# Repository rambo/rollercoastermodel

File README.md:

rollercoastermodel
==================

Schematics and Arduino code related to a model rollercoaster

This was done to help Stadi Mallarit to get some new tools by building the model
to company X (I'll check later if they want their name released).

I ran out of time so some features (like adjusting each LED channel via the menu)
are not implemented at all, and the state machine for the menu in general is a bit
of a mess. It does work though.

The reason for some "weirdness" in the schematics of the IO boards is that those
were built on veroboard (in retrospect it would have been faster to make proper boards
even with all the drilling involved).

If I end up doing this menu thing better in some other project I'll come back here
and add a link, meanwhile: Be brave even if it looks like a horrible mess, there is some
decent stuff hidden in there.

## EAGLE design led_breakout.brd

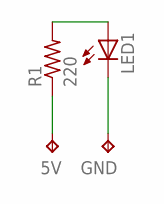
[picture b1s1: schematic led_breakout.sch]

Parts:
5V: TPTP13R; TP13R
GND: TPTP13SQ; TP13SQ
LED1: LEDSML0603; SML0603
R1: 220; R0603

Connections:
5V: 5V.TP, R1.1
GND: GND.TP, LED1.C
LEDSUPPLY: LED1.A, R1.2

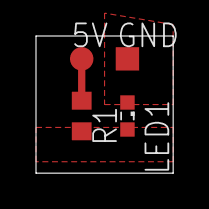
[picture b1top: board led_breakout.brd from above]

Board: 2 copper layers, 7.6 x 7.6 mm, 4 parts (0 on the bottom side), 3 nets.

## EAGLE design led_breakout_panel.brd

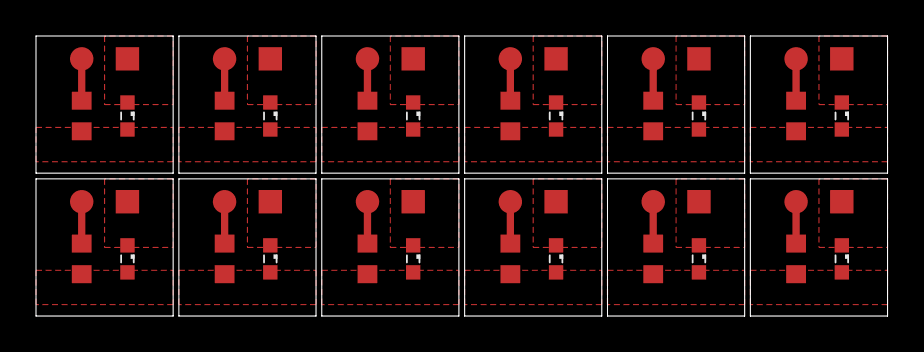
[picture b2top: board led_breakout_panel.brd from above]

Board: 2 copper layers, 47.3 x 15.6 mm, 48 parts (0 on the bottom side), 36 nets.

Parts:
5V, 5V1, 5V2, 5V3, 5V4, 5V5, 5V6, 5V7, 5V8, 5V9, 5V10, 5V11: TPTP13R; TP13R
GND, GND1, GND2, GND3, GND4, GND5, GND6, GND7, GND8, GND9, GND10, GND11: TPTP13SQ; TP13SQ
LED1, LED2, LED3, LED4, LED5, LED6, LED7, LED8, LED9, LED10, LED11, LED12: SML0603
R1, R2, R3, R4, R5, R6, R7, R8, R9, R10, R11, R12: 220; R0603

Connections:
5V: 5V.TP, R1.1
5V1: 5V1.TP, R2.1
5V2: 5V2.TP, R3.1
5V3: 5V3.TP, R4.1
5V4: 5V4.TP, R5.1
5V5: 5V5.TP, R6.1
5V6: 5V6.TP, R7.1
5V7: 5V7.TP, R8.1
5V8: 5V8.TP, R9.1
5V9: 5V9.TP, R10.1
5V10: 5V10.TP, R11.1
5V11: 5V11.TP, R12.1
GND: GND.TP, LED1.C
GND1: GND1.TP, LED2.C
GND2: GND2.TP, LED3.C
GND3: GND3.TP, LED4.C
GND4: GND4.TP, LED5.C
GND5: GND5.TP, LED6.C
GND6: GND6.TP, LED7.C
GND7: GND7.TP, LED8.C
GND8: GND8.TP, LED9.C
GND9: GND9.TP, LED10.C
GND10: GND10.TP, LED11.C
GND11: GND11.TP, LED12.C
LEDSUPPLY: LED1.A, R1.2
LEDSUPPLY1: LED2.A, R2.2
LEDSUPPLY2: LED3.A, R3.2
LEDSUPPLY3: LED4.A, R4.2
LEDSUPPLY4: LED5.A, R5.2
LEDSUPPLY5: LED6.A, R6.2
LEDSUPPLY6: LED7.A, R7.2
LEDSUPPLY7: LED8.A, R8.2
LEDSUPPLY8: LED9.A, R9.2
LEDSUPPLY9: LED10.A, R10.2
LEDSUPPLY10: LED11.A, R11.2
LEDSUPPLY11: LED12.A, R12.2

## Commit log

2013-11-16 simple breakout
2013-11-16 panelized
2013-11-16 tighter package
2013-11-16 tighter panel
2013-11-16 stub
2013-11-16 shift-register LCD test
2013-11-16 trying to get shiftpwm working
2013-11-16 wtf, there is still some fading happening though all of the LEDs should be full-on
2013-11-16 the library works, I had forgotten to connect reset to vcc so the register was resetting at random
2013-11-16 this was a no-op and it looks better like this anyway
2013-11-16 3Wire version is designed for 595 specifically and gives us backlight control as well
2013-11-17 use SR3W version with backlight control
2013-11-17 schematic for reference, I will build this on veroboard
2013-11-17 added a note about current limiting on the backlight
2013-11-17 reminder
2013-11-17 the way it was actually built on veroboard
2013-11-17 this should be the correct pinmap bu I get nothing (not even the backlight...)
2013-11-17 keep schematic and sketch consistent
2013-11-17 maybe it was zero based afterall ??
2013-11-17 do not blink anymore, thigns work, no need to test
2013-11-17 some more pins swapped
2013-11-17 add support for the rotary encoder
2013-11-17 free a HW-PWM pin
2013-11-17 tested motor control
2013-11-17 schematic for breaking out the shift registers for SW-PWM of leds and HW-PWM for motor
2013-11-17 added the darlington and pin-headers for outputs
2013-11-17 bring 12V in trhough this board, use 4 wires to pass the 12V to the arduino and 5V back
2013-11-17 tested that the new board with daisy-chained 595s works
2013-11-17 these got switched around
2013-11-17 reminders
2013-11-17 stubs
2013-11-17 started writing the proper software
2013-11-17 keep this stub task from robbing priority
2013-11-17 started working on the global config/state system
2013-11-17 it is an array, this pointing method also compiles, I wonder whether it actually works...
2013-11-17 hey, it works
2013-11-17 simple motor control state machine
2013-11-17 refactor the configs to a separate file
2013-11-17 test global dimmer
2013-11-17 avoid blinding myself when testing
2013-11-17 fix a brainfart with the global adjust
2013-11-17 sleep and wakeup states, still thinking about the best way to handle the menu
2013-11-17 work in progress
2013-11-17 too tired to figure out the new way to do this, thus including with the compat macro defined...
2013-11-17 this ought to be the correct way
2013-11-17 menu rotation would work if I got correct data on screen...
2013-11-17 based on my other test this ought to work
2013-11-17 am I running low on something else here ?? I get binary crap on the prints but very similar approeach works fine in a standalone sketch
2013-11-17 new macro to solve the array access probelm
2013-11-17 return so the next iteration can start in new state
2013-11-18 wrap the menu, use constant for the menu size
2013-11-18 started working on the submenus
2013-11-18 general menu logic hardning, dimmer menu
2013-11-18 default to back
2013-11-18 started working on the motor menu
2013-11-18 motor timer editor
2013-11-18 motor speed editor
2013-11-18 save menu implemented
2013-11-18 updated schematic to correspond with reality
2013-11-18 some notes
2013-11-18 quickview versions of the schematics
2013-11-18 updated description
2013-11-18 image (poor one but the best I had) of the wiring connections
2013-11-18 note about this being the ugly one
2013-11-18 not money, tools (but those are worth money, so it is a matter of semantics mainly)
